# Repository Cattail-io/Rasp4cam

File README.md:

# Rasp4cam
<p>
Multi Camera Adapter for Raspberry Pi (Kicad v5.xx)
<p>

Simple camera multiplexer for Raspberry Pi allowed to connect up to 4 cameras to single CSI port. Only ONE camera can be enabled at a time. 

Reversed from [site](https://www.arducam.com/multi-camera-adapter-module-raspberry-pi/). 
Usage:
```
import RPi.GPIO as gp
import os

gp.setwarnings(False)
gp.setmode(gp.BOARD)

gp.setup(7, gp.OUT)
gp.setup(11, gp.OUT)
gp.setup(12, gp.OUT)

gp.setup(15, gp.OUT)
gp.setup(16, gp.OUT)
gp.setup(21, gp.OUT)
gp.setup(22, gp.OUT)

gp.output(11, True)
gp.output(12, True)
gp.output(15, True)
gp.output(16, True)
gp.output(21, True)
gp.output(22, True)

def main():
    gp.output(7, False)
    gp.output(11, False)
    gp.output(12, True)
    capture(1)

    gp.output(7, True)
    gp.output(11, False)
    gp.output(12, True)
    capture(2)

    gp.output(7, False)
    gp.output(11, True)
    gp.output(12, False)
    capture(3)

    gp.output(7, True)
    gp.output(11, True)
    gp.output(12, False)
    capture(4)

def capture(cam):
    cmd = "raspistill -o capture_%d.jpg" % cam
    os.system(cmd)

if __name__ == "__main__":
    main()

    gp.output(7, False)
    gp.output(11, False)
    gp.output(12, True)
```

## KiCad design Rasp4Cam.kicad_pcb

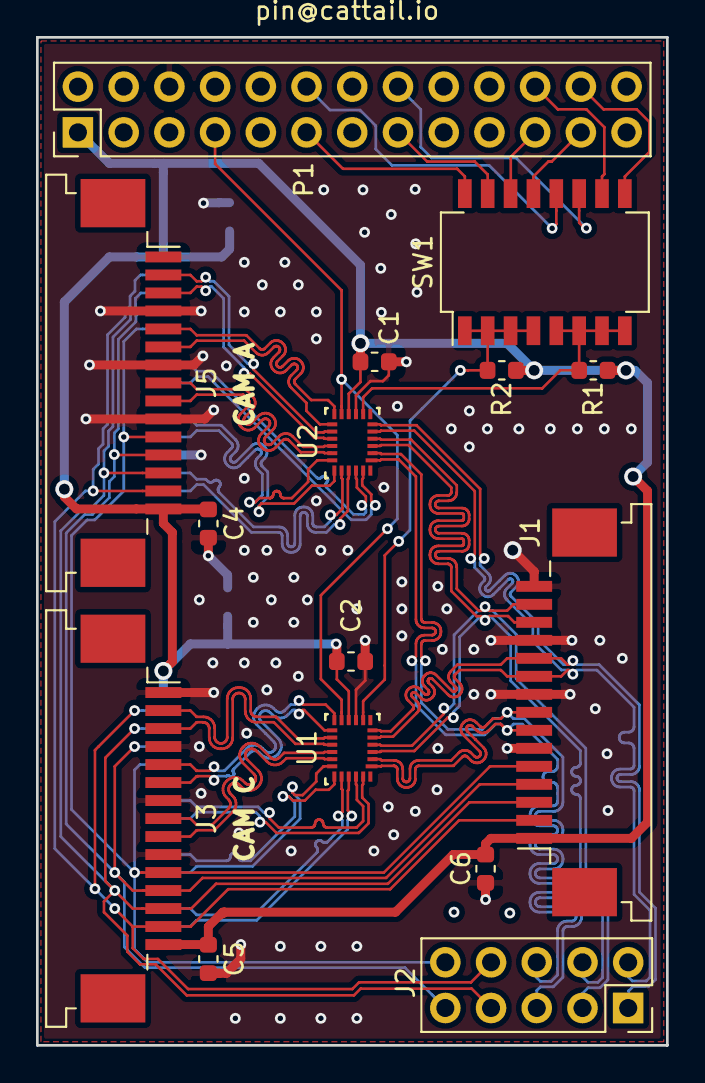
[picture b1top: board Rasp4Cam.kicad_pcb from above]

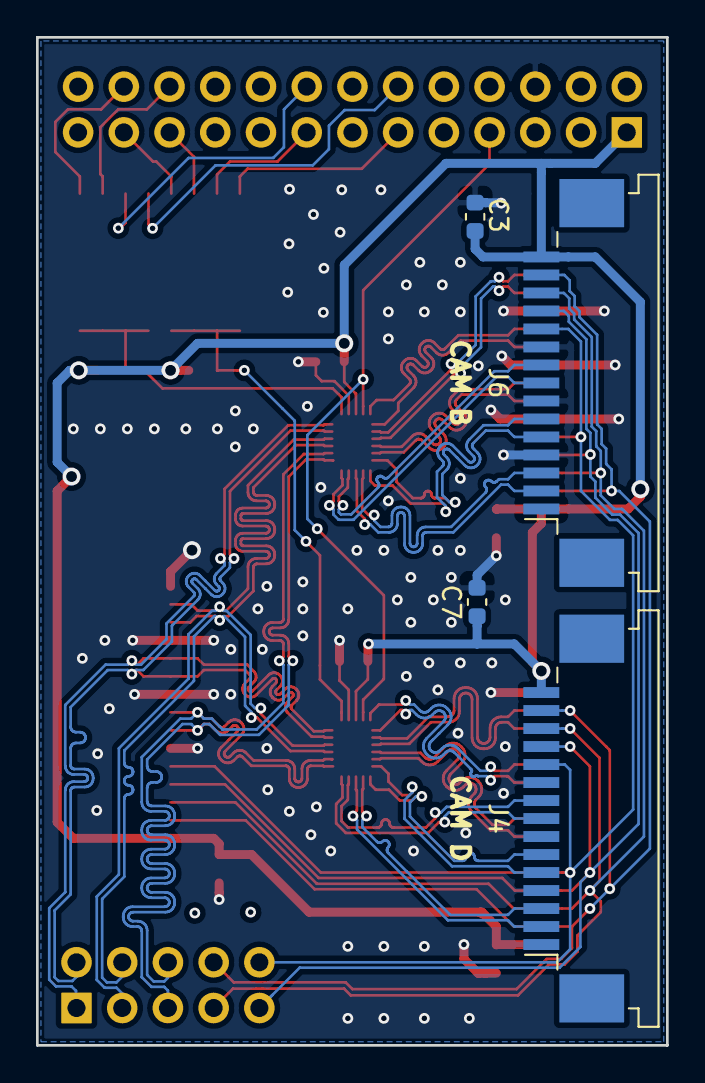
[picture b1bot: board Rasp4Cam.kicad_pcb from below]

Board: 2 copper layers, 35.0 x 56.0 mm, 19 parts (4 on the bottom side), 47 nets.

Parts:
C1, C2, C3, C4, C5, C6, C7: 100nF; C_0603_1608Metric
J1, J3, J4, J5, J6: Conn_01x15; TE_1-84953-5_1x15-1MP_P1.0mm_Horizontal
J2: Conn_02x05_Odd_Even; PinSocket_2x05_P2.54mm_Vertical
P1: CONN_13X2; PinHeader_2x13_P2.54mm_Vertical
R1, R2: 10k; R_0603_1608Metric
SW1: SW_DIP_x08; SW_DIP_SPSTx08_Slide_Copal_CHS-08B_W7.62mm_P1.27mm
U1, U2: FSA642; UMLP-24_2.4x3.4_Pitch0.4mm

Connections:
+3V3: C1.1, C2.1, C3.1, C4.1, C5.1, C6.1, C7.1, J1.1, J3.15, J4.15, J5.15, J6.15, P1.1, R1.1, R2.1, U1.10, U2.10
/CAMA_C+: J3.9, U1.17
/CAMA_C-: J3.8, U1.16
/CAMA_D0+: J3.3, U1.15
/CAMA_D0-: J3.2, U1.14
/CAMA_D1+: J3.6, U1.13
/CAMA_D1-: J3.5, U1.12
/CAMB_C+: J4.9, U1.22
/CAMB_C-: J4.8, U1.23
/CAMB_D0+: J4.3, U1.20
/CAMB_D0-: J4.2, U1.21
/CAMB_D1+: J4.6, U1.19
/CAMB_D1-: J4.5, U1.18
/CAMC_C+: J5.9, U2.17
/CAMC_C-: J5.8, U2.16
/CAMC_D0+: J5.3, U2.15
/CAMC_D0-: J5.2, U2.14
/CAMC_D1+: J5.6, U2.13
/CAMC_D1-: J5.5, U2.12
/CAMD_C+: J6.9, U2.22
/CAMD_C-: J6.8, U2.23
/CAMD_D0+: J6.3, U2.20
/CAMD_D0-: J6.2, U2.21
/CAMD_D1+: J6.6, U2.19
/CAMD_D1-: J6.5, U2.18
/CAM_C+: J1.7, J2.6, U1.1, U2.1
/CAM_C-: J1.8, J2.5, U1.2, U2.2
/CAM_CLK: J1.4, J2.9, J3.12, J4.12, J5.12, J6.12
/CAM_D0+: J1.13, J2.4, U1.3, U2.3
/CAM_D0-: J1.14, J2.3, U1.4, U2.4
/CAM_D1+: J1.10, J2.2, U1.5, U2.5
/CAM_D1-: J1.11, J2.1, U1.6, U2.6
/CAM_GPIO: J1.5, J2.10, J3.11, J4.11, J5.11, J6.11
/GPIO4: P1.7, U1.11, U2.11
/GPIO8: P1.24, SW1.9
/GPIO9: P1.21, SW1.14
/GPIO11: P1.23, SW1.13
/GPIO17: P1.11, SW1.16
/GPIO18: P1.12, SW1.12
/GPIO22: P1.15, SW1.15
/GPIO23: P1.16, SW1.11
/GPIO25: P1.22, SW1.10
/OE1: R2.2, SW1.1, SW1.2, SW1.3, SW1.4, U1.8
/OE2: R1.2, SW1.5, SW1.6, SW1.7, SW1.8, U2.8
/SCL0: J1.3, J2.7, J3.13, J4.13, J5.13, J6.13
/SDA0: J1.2, J2.8, J3.14, J4.14, J5.14, J6.14
GND: C1.2, C2.2, C3.2, C4.2, C5.2, C6.2, C7.2, J1.6, J1.9, J1.12, J1.15, J3.1, J3.4, J3.7, J3.10, J4.1, J4.4, J4.7, J4.10, J5.1, J5.4, J5.7, J5.10, J6.1, J6.4, J6.7, J6.10, P1.6, U1.9, U2.9
